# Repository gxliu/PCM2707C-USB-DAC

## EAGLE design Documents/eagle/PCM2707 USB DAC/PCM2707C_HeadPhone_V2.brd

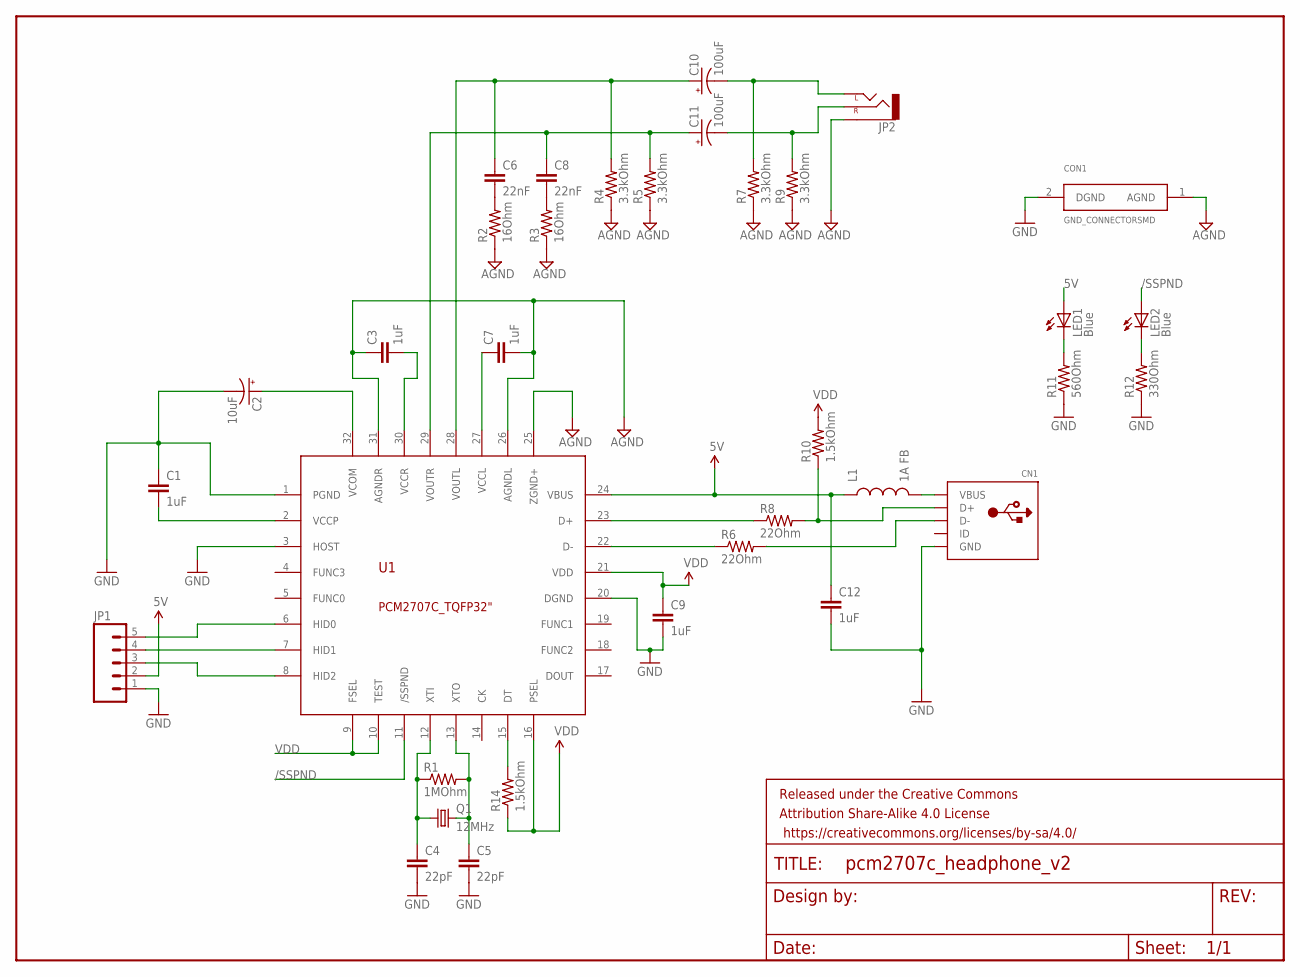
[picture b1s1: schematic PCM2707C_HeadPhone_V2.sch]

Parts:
C1, C3, C7, C9, C12: 1uF; 0805
C2: 10uF; PANASONIC_C
C4, C5: 22pF; 0805
C6, C8: 22nF; 0805
C10, C11: 100uF; PANASONIC_C
CN1: USBMOLEX; USB-MINIB-THM-MOLEX
CON1: GND_CONNECTORSMD; GND_CONNECTOR
FRAME1: FRAME-LETTER; CREATIVE_COMMONS
JP1: M05LOCK; 1X05_LOCK
JP2: AUDIO-JACKPTH; AUDIO-JACK
L1: 1A FB; 0805
LED1, LED2: Blue; LED-0603
Q1: 12MHz; HC49U-V
R1: 1MOhm; 0805
R2, R3: 16Ohm; 0805
R4, R5, R7, R9: 3.3kOhm; 0805
R6, R8: 22Ohm; 0805
R10, R14: 1.5kOhm; 0805
R11: 560Ohm; 0805
R12: 330Ohm; 0805
U1: PCM2707C_TQFP32"; 32TQFP_PCM2707C

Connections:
5V: C12.1, JP1.2, L1.1, LED1.A, U1.24 (VBUS)
/SSPND: LED2.A, U1.11 (/SSPND)
AGND: C3.1, C7.2, CON1.1 (AGND), JP2.SLEEVE, R2.1, R3.1, R4.1, R5.1, R7.1, R9.1, U1.25 (ZGND+), U1.26 (AGNDL), U1.31 (AGNDR)
GND: C1.1, C2.-, C4.2, C5.2, C9.2, C12.2, CN1.GND, CON1.2 (DGND), JP1.1, R11.1, R12.1, U1.1 (PGND), U1.3 (HOST), U1.20 (DGND)
unnamed: JP1.5, U1.6 (HID0)
unnamed: C1.2, U1.2 (VCCP)
unnamed: JP1.4, U1.7 (HID1)
unnamed: C2.+, U1.32 (VCOM)
unnamed: JP1.3, U1.8 (HID2)
unnamed: CN1.VBUS, L1.2
unnamed: C4.1, Q1.1, R1.1, U1.12 (XTI)
unnamed: C5.1, Q1.2, R1.2, U1.13 (XTO)
unnamed: R8.1, U1.23 (D+)
unnamed: R6.1, U1.22 (D-)
unnamed: CN1.D+, R8.2, R10.1
unnamed: CN1.D-, R6.2
unnamed: C3.2, U1.30 (VCCR)
unnamed: LED1.C, R11.2
unnamed: R14.2, U1.15 (DT)
unnamed: C7.1, U1.27 (VCCL)
unnamed: C8.2, R3.2
unnamed: C6.2, R2.2
unnamed: C11.-, JP2.RING (RIGHT), R9.2
unnamed: C10.-, JP2.TIP (LEFT), R7.2
unnamed: C8.1, C11.+, R5.2, U1.29 (VOUTR)
unnamed: LED2.C, R12.2
unnamed: C6.1, C10.+, R4.2, U1.28 (VOUTL)
VDD: C9.1, R10.2, R14.1, U1.9 (FSEL), U1.10 (TEST), U1.16 (PSEL), U1.21 (VDD)

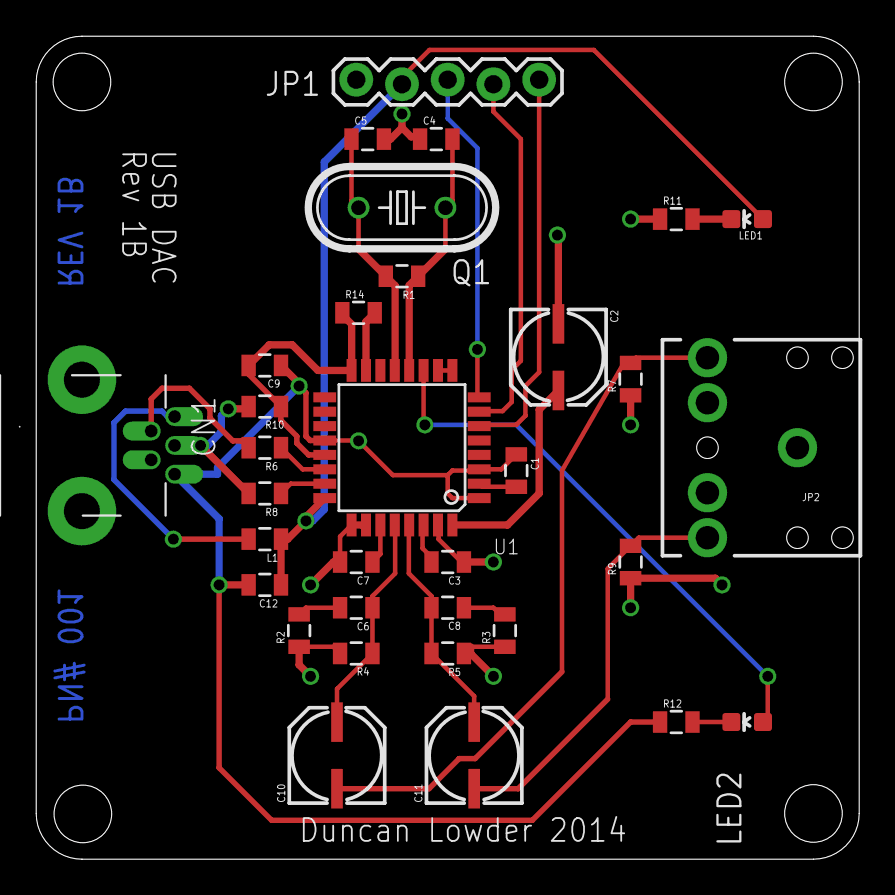
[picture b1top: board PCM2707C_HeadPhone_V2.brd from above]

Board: 2 copper layers, 45.7 x 45.7 mm, 35 parts (1 on the bottom side), 28 nets.

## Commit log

2014-08-05 Add Eagle Files

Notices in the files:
parts and their libraries:
SparkFun-Passives: Licensing: Creative Commons ShareAlike 4.0 International - https://creativecommons.org/licenses/by-sa/4.0
SparkFun-Aesthetics: Released under the Creative Commons Attribution Share-Alike 4.0 License
SparkFun-Aesthetics: https://creativecommons.org/licenses/by-sa/4.0
